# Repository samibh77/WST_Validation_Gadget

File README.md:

# WST_Validation_Gadget

## 📌 Project Overview
The WST Gadget is a modular, IoT-based device developed by WaterSec to enhance the accuracy and reliability of water monitoring systems. It addresses critical challenges such as sensor calibration, LoRa transmission optimization, and noise interference, ensuring efficient and precise water usage data collection.

## ⚙️ Features
• Sensor Calibration & Validation: Ensures accurate flowmeter readings by adjusting calibration parameters.

• LoRa Transmission Power Optimization: Dynamically adjusts transmission power for energy efficiency and reliable communication.

• Noise Detection: Identifies and mitigates false impulses caused by neighboring sensors.

## 🛠️ System Architecture

The WST Gadget's software is structured into the following main modules:

• Sensor Calibration & Validation: Measures and adjusts flowmeter calibration.

• LoRa Transmission Power Optimization: Tests and adjusts LoRa transmission power.

• Noise Detection: Identifies and compensates for noise interference.

• User Interface: Provides feedback and configuration options.

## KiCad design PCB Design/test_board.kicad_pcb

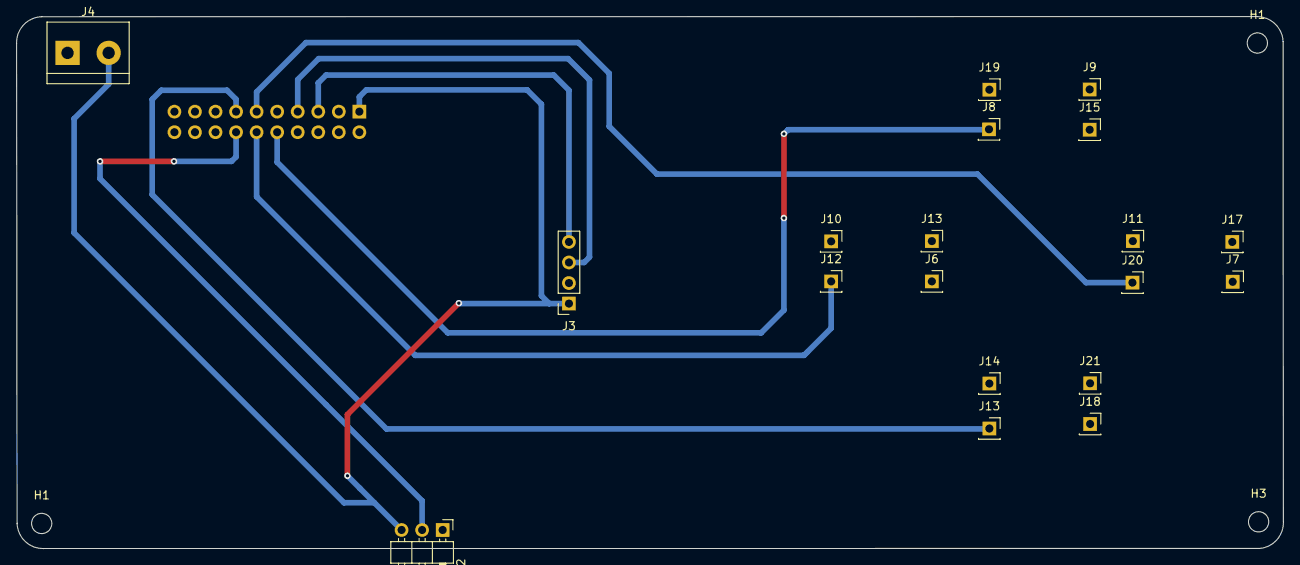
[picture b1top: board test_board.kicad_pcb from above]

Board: 2 copper layers, 156.6 x 65.8 mm, 23 parts (1 on the bottom side), 9 nets.

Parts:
H1, H1#2, H3: MountingHole; MountingHole_2.5mm
J1: Conn_02x05_Odd_Even; PinSocket_2x10_P2.54mm_Vertical
J2: Conn_01x03; PinHeader_1x03_P2.54mm_Horizontal
J3: Conn_01x04; PinSocket_1x04_P2.54mm_Vertical
J4: Conn_01x02; TerminalBlock_bornier-2_P5.08mm
J6, J7, J8, J9, J10, J11, J12, J13, J13#2, J14, J15, J17, J18, J19, J20, J21: Conn_01x01; PinSocket_1x01_P2.54mm_Vertical

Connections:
+5V: J1.1, J2.3, J3.1, J4.2
GND: J1.2, J2.1, J3.2, J4.1, J9.1, J13#2.1, J17.1, J21.1
GPIO4: J1.5, J3.4
GPIO6: J1.7, J3.3
GPIO7: J1.10, J8.1
GPIO9: J1.12, J12.1
GPIO10: J1.11, J20.1
GPIO11: J1.14, J2.2
GPIO12: J1.13, J13.1

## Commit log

2025-09-22 add files
2025-09-23 update files
